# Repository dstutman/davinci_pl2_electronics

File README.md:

# Payload 2 for the DaVinci cubesat

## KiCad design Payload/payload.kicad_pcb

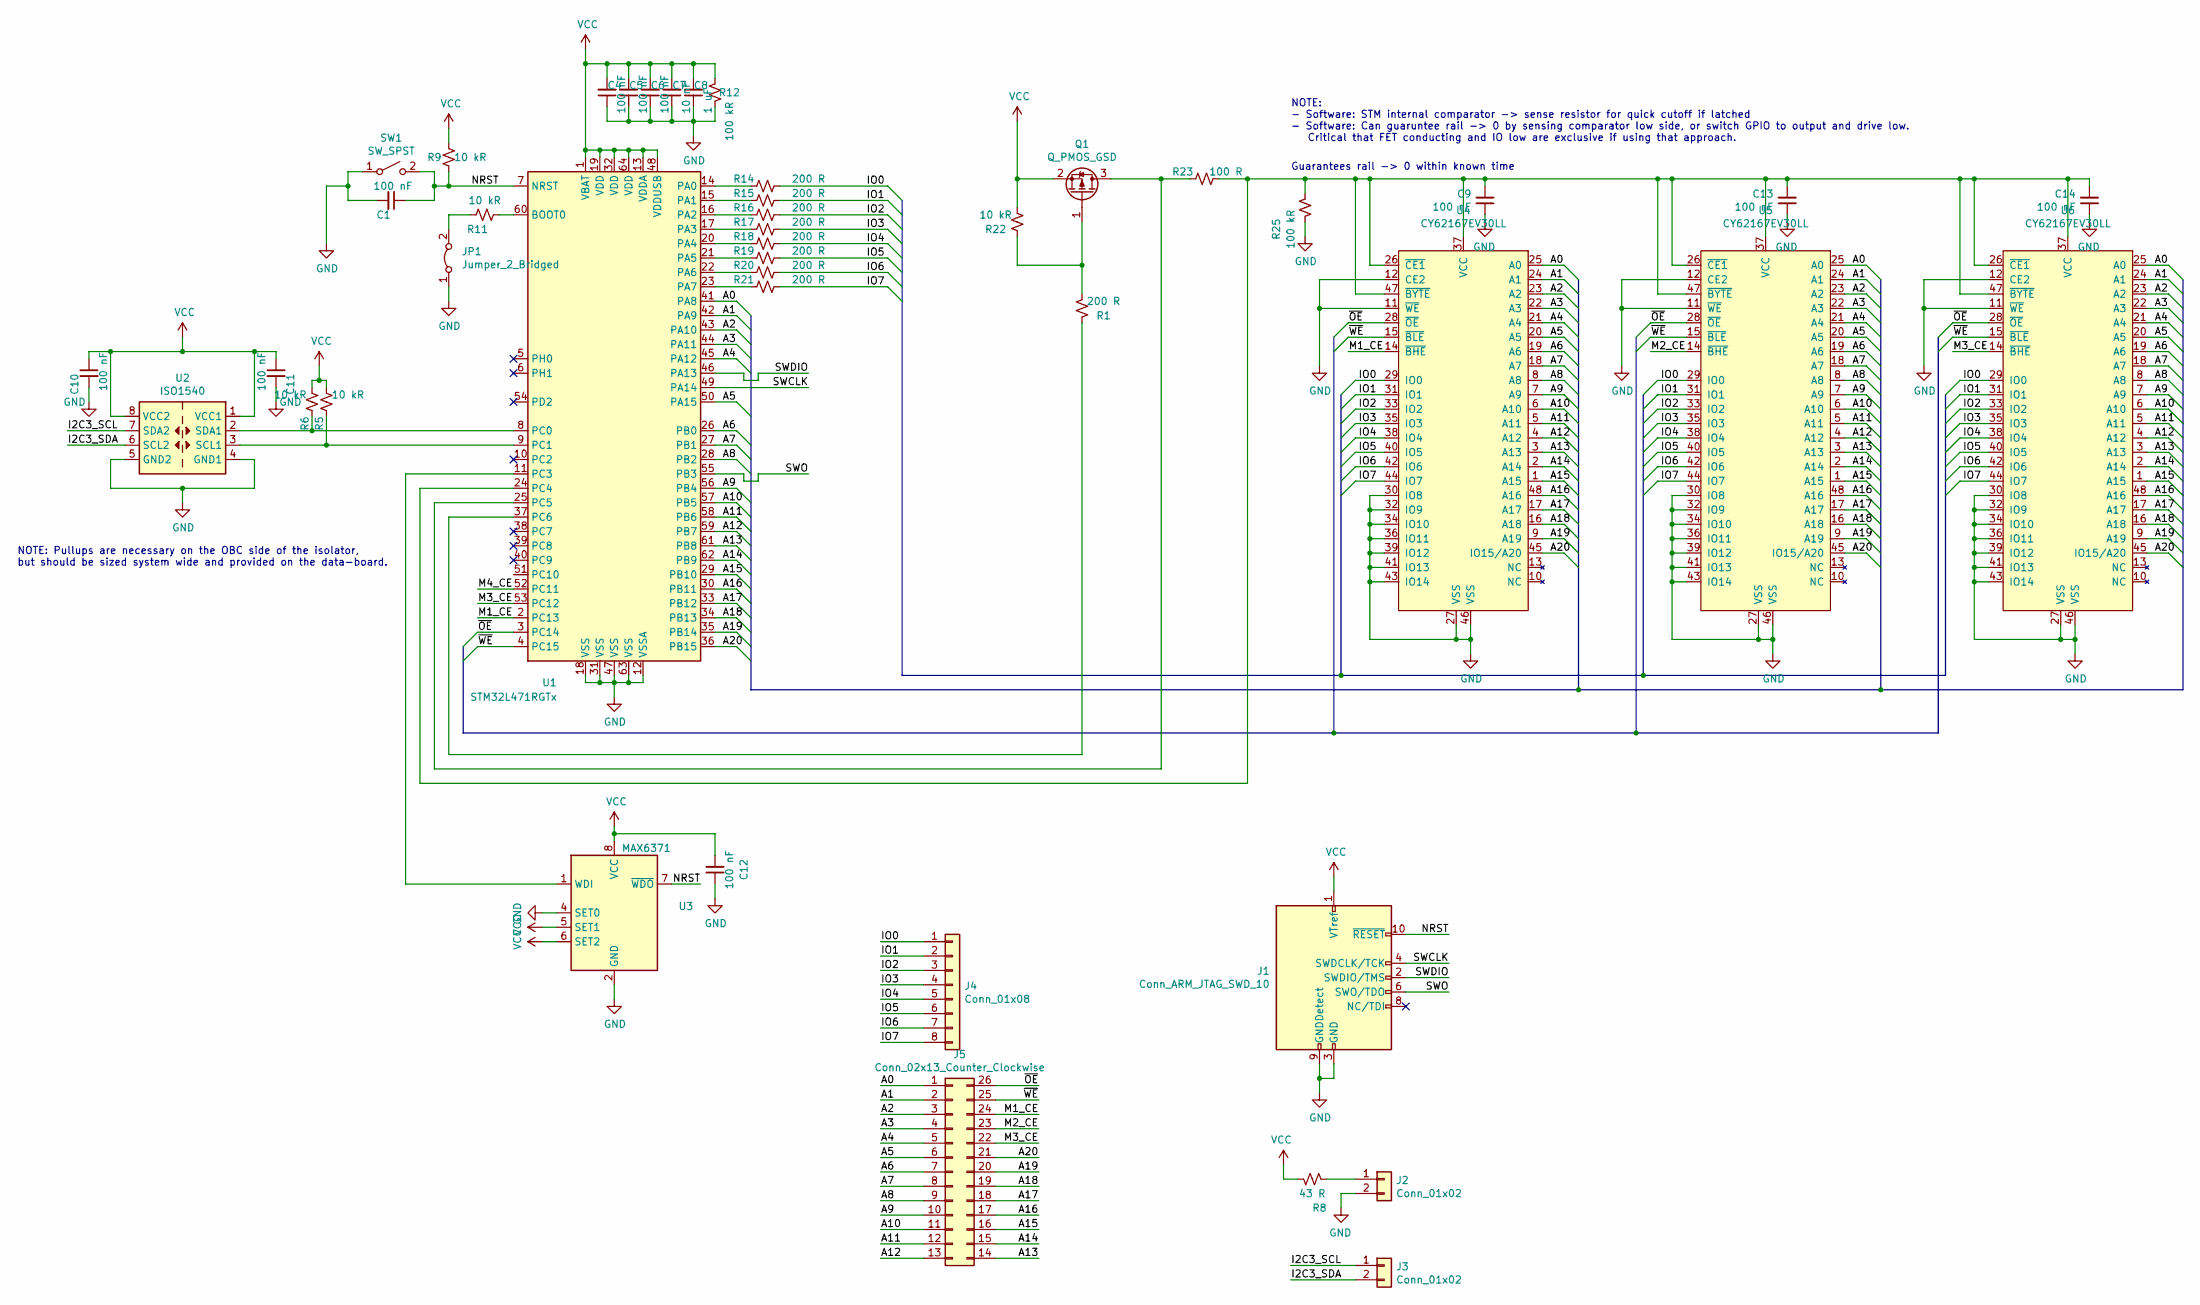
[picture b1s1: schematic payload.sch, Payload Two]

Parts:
C1, C4, C5, C6, C9, C10, C11, C12, C13, C14: 100 nF; C_0603_1608Metric
C7: 10 nF; C_0603_1608Metric
C8: 1 uF; C_0603_1608Metric
J1: Conn_ARM_JTAG_SWD_10; PinHeader_2x05_P1.27mm_Vertical
J2, J3: Conn_01x02; SolderWire-0.25sqmm_1x02_P4.5mm_D0.65mm_OD2mm
J4: Conn_01x08; PinHeader_1x08_P1.27mm_Vertical
J5: Conn_02x13_Counter_Clockwise; PinHeader_2x13_P1.27mm_Vertical
JP1: Jumper_2_Bridged; SolderJumper-2_P1.3mm_Bridged2Bar_RoundedPad1.0x1.5mm
Q1: Q_PMOS_GSD; SOT-23
R1, R14, R15, R16, R17, R18, R19, R20, R21: 200 R; R_0603_1608Metric
R5, R6, R9, R11, R22: 10 kR; R_0603_1608Metric
R8: 43 R; R_0603_1608Metric
R12, R25: 100 kR; R_0603_1608Metric
R23: 100 R; R_0603_1608Metric
SW1: SW_SPST; SW_SPST_PTS810
U1: STM32L471RGTx; LQFP-64_10x10mm_P0.5mm
U2: ISO1540; SOIC-8_3.9x4.9mm_P1.27mm
U3: MAX6371; SOT-23-8
U4, U5, U6: CY62167EV30LL; TSOP-I-48_18.4x12mm_P0.5mm

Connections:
/A0: J5.1, U1.41 (PA8), U4.25 (A0), U5.25 (A0), U6.25 (A0)
/A1: J5.2, U1.42 (PA9), U4.24 (A1), U5.24 (A1), U6.24 (A1)
/A2: J5.3, U1.43 (PA10), U4.23 (A2), U5.23 (A2), U6.23 (A2)
/A3: J5.4, U1.44 (PA11), U4.22 (A3), U5.22 (A3), U6.22 (A3)
/A4: J5.5, U1.45 (PA12), U4.21 (A4), U5.21 (A4), U6.21 (A4)
/A5: J5.6, U1.50 (PA15), U4.20 (A5), U5.20 (A5), U6.20 (A5)
/A6: J5.7, U1.26 (PB0), U4.19 (A6), U5.19 (A6), U6.19 (A6)
/A7: J5.8, U1.27 (PB1), U4.18 (A7), U5.18 (A7), U6.18 (A7)
/A8: J5.9, U1.28 (PB2), U4.8 (A8), U5.8 (A8), U6.8 (A8)
/A9: J5.10, U1.56 (PB4), U4.7 (A9), U5.7 (A9), U6.7 (A9)
/A10: J5.11, U1.57 (PB5), U4.6 (A10), U5.6 (A10), U6.6 (A10)
/A11: J5.12, U1.58 (PB6), U4.5 (A11), U5.5 (A11), U6.5 (A11)
/A12: J5.13, U1.59 (PB7), U4.4 (A12), U5.4 (A12), U6.4 (A12)
/A13: J5.14, U1.61 (PB8), U4.3 (A13), U5.3 (A13), U6.3 (A13)
/A14: J5.15, U1.62 (PB9), U4.2 (A14), U5.2 (A14), U6.2 (A14)
/A15: J5.16, U1.29 (PB10), U4.1 (A15), U5.1 (A15), U6.1 (A15)
/A16: J5.17, U1.30 (PB11), U4.48 (A16), U5.48 (A16), U6.48 (A16)
/A17: J5.18, U1.33 (PB12), U4.17 (A17), U5.17 (A17), U6.17 (A17)
/A18: J5.19, U1.34 (PB13), U4.16 (A18), U5.16 (A18), U6.16 (A18)
/A19: J5.20, U1.35 (PB14), U4.9 (A19), U5.9 (A19), U6.9 (A19)
/A20: J5.21, U1.36 (PB15), U4.45 (IO15/A20), U5.45 (IO15/A20), U6.45 (IO15/A20)
/I2C3_SCL: J3.1, U2.7 (SDA2)
/I2C3_SDA: J3.2, U2.6 (SCL2)
/IO0: J4.1, R14.1, U4.29 (IO0), U5.29 (IO0), U6.29 (IO0)
/IO1: J4.2, R15.1, U4.31 (IO1), U5.31 (IO1), U6.31 (IO1)
/IO2: J4.3, R16.1, U4.33 (IO2), U5.33 (IO2), U6.33 (IO2)
/IO3: J4.4, R17.1, U4.35 (IO3), U5.35 (IO3), U6.35 (IO3)
/IO4: J4.5, R18.1, U4.38 (IO4), U5.38 (IO4), U6.38 (IO4)
/IO5: J4.6, R19.1, U4.40 (IO5), U5.40 (IO5), U6.40 (IO5)
/IO6: J4.7, R20.1, U4.42 (IO6), U5.42 (IO6), U6.42 (IO6)
/IO7: J4.8, R21.1, U4.44 (IO7), U5.44 (IO7), U6.44 (IO7)
/M1_CE: J5.24, U1.2 (PC13), U4.14 (~BHE)
/M2_CE: J5.23, U5.14 (~BHE)
/M3_CE: J5.22, U1.53 (PC12), U6.14 (~BHE)
/M4_CE: U1.52 (PC11)
/NRST: C1.1, J1.10 (~RESET~), R9.2, SW1.2 (B), U1.7 (NRST), U3.7 (~WDO)
/SWCLK: J1.4 (SWDCLK/TCK), U1.49 (PA14)
/SWDIO: J1.2 (SWDIO/TMS), U1.46 (PA13)
/SWO: J1.6 (SWO/TDO), U1.55 (PB3)
/~OE: J5.26, U1.3 (PC14), U4.28 (~OE), U5.28 (~OE), U6.28 (~OE)
/~WE: J5.25, U1.4 (PC15), U4.15 (~BLE), U5.15 (~BLE), U6.15 (~BLE)
GND: C1.2, C4.1, C5.1, C6.1, C7.1, C8.1, C9.1, C10.2, C11.2, C12.1, C13.1, C14.1, J1.3 (GND), J1.5 (GND), J1.9 (GNDDetect), J2.2, JP1.1 (A), R12.2, R25.2, SW1.1 (A), U1.12 (VSSA), U1.18 (VSS), U1.31 (VSS), U1.47 (VSS), U1.63 (VSS), U2.4 (GND1), U2.5 (GND2), U3.2 (GND), U3.4 (SET0), U4.11 (~WE), U4.12 (CE2), U4.27 (VSS), U4.30 (IO8), U4.32 (IO9), U4.34 (IO10), U4.36 (IO11), U4.39 (IO12), U4.41 (IO13), U4.43 (IO14), U4.46 (VSS), U5.11 (~WE), U5.12 (CE2), U5.27 (VSS), U5.30 (IO8), U5.32 (IO9), U5.34 (IO10), U5.36 (IO11), U5.39 (IO12), U5.41 (IO13), U5.43 (IO14), U5.46 (VSS), U6.11 (~WE), U6.12 (CE2), U6.27 (VSS), U6.30 (IO8), U6.32 (IO9), U6.34 (IO10), U6.36 (IO11), U6.39 (IO12), U6.41 (IO13), U6.43 (IO14), U6.46 (VSS)
unnamed: C9.2, C13.2, C14.2, R23.2, R25.1, U1.24 (PC4), U4.26 (~CE1), U4.37 (VCC), U4.47 (~BYTE), U5.26 (~CE1), U5.37 (VCC), U5.47 (~BYTE), U6.26 (~CE1), U6.37 (VCC), U6.47 (~BYTE)
unnamed: J2.1, R8.2
unnamed: JP1.2 (B), R11.1
unnamed: Q1.1 (G), R1.2, R22.1
unnamed: Q1.3 (D), R23.1, U1.25 (PC5)
unnamed: R1.1, U1.37 (PC6)
unnamed: R5.2, U1.9 (PC1), U2.3 (SCL1)
unnamed: R6.2, U1.8 (PC0), U2.2 (SDA1)
unnamed: R11.2, U1.60 (BOOT0)
unnamed: R14.2, U1.14 (PA0)
unnamed: R15.2, U1.15 (PA1)
unnamed: R16.2, U1.16 (PA2)
unnamed: R17.2, U1.17 (PA3)
unnamed: R18.2, U1.20 (PA4)
unnamed: R19.2, U1.21 (PA5)
unnamed: R20.2, U1.22 (PA6)
unnamed: R21.2, U1.23 (PA7)
unnamed: U1.11 (PC3), U3.1 (WDI)
VCC: C4.2, C5.2, C6.2, C7.2, C8.2, C10.1, C11.1, C12.2, J1.1 (VTref), Q1.2 (S), R5.1, R6.1, R8.1, R9.1, R12.1, R22.2, U1.1 (VBAT), U1.13 (VDDA), U1.19 (VDD), U1.32 (VDD), U1.48 (VDDUSB), U1.64 (VDD), U2.1 (VCC1), U2.8 (VCC2), U3.5 (SET1), U3.6 (SET2), U3.8 (VCC)

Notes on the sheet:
NOTE: - Software: STM internal comparator -> sense resistor for quick cutoff if latched - Software: Can guaruntee rail -> 0 by sensing comparator low side, or switch GPIO to output and drive low. Critical that FET conducting and IO low are exclusive if using that approach.
Guarantees rail -> 0 within known time
NOTE: Pullups are necessary on the OBC side of the isolator, but should be sized system wide and provided on the data-board.

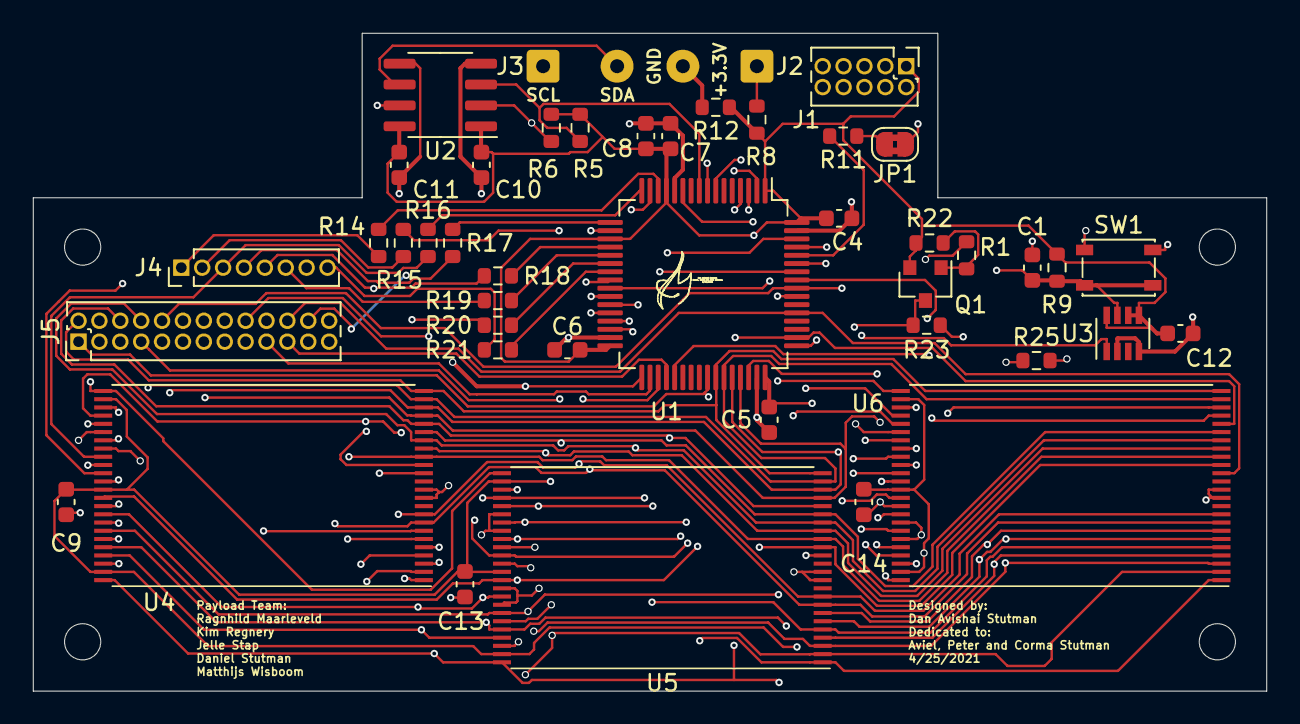
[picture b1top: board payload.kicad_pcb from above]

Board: 4 copper layers, 75.0 x 40.0 mm, 44 parts (0 on the bottom side), 60 nets.

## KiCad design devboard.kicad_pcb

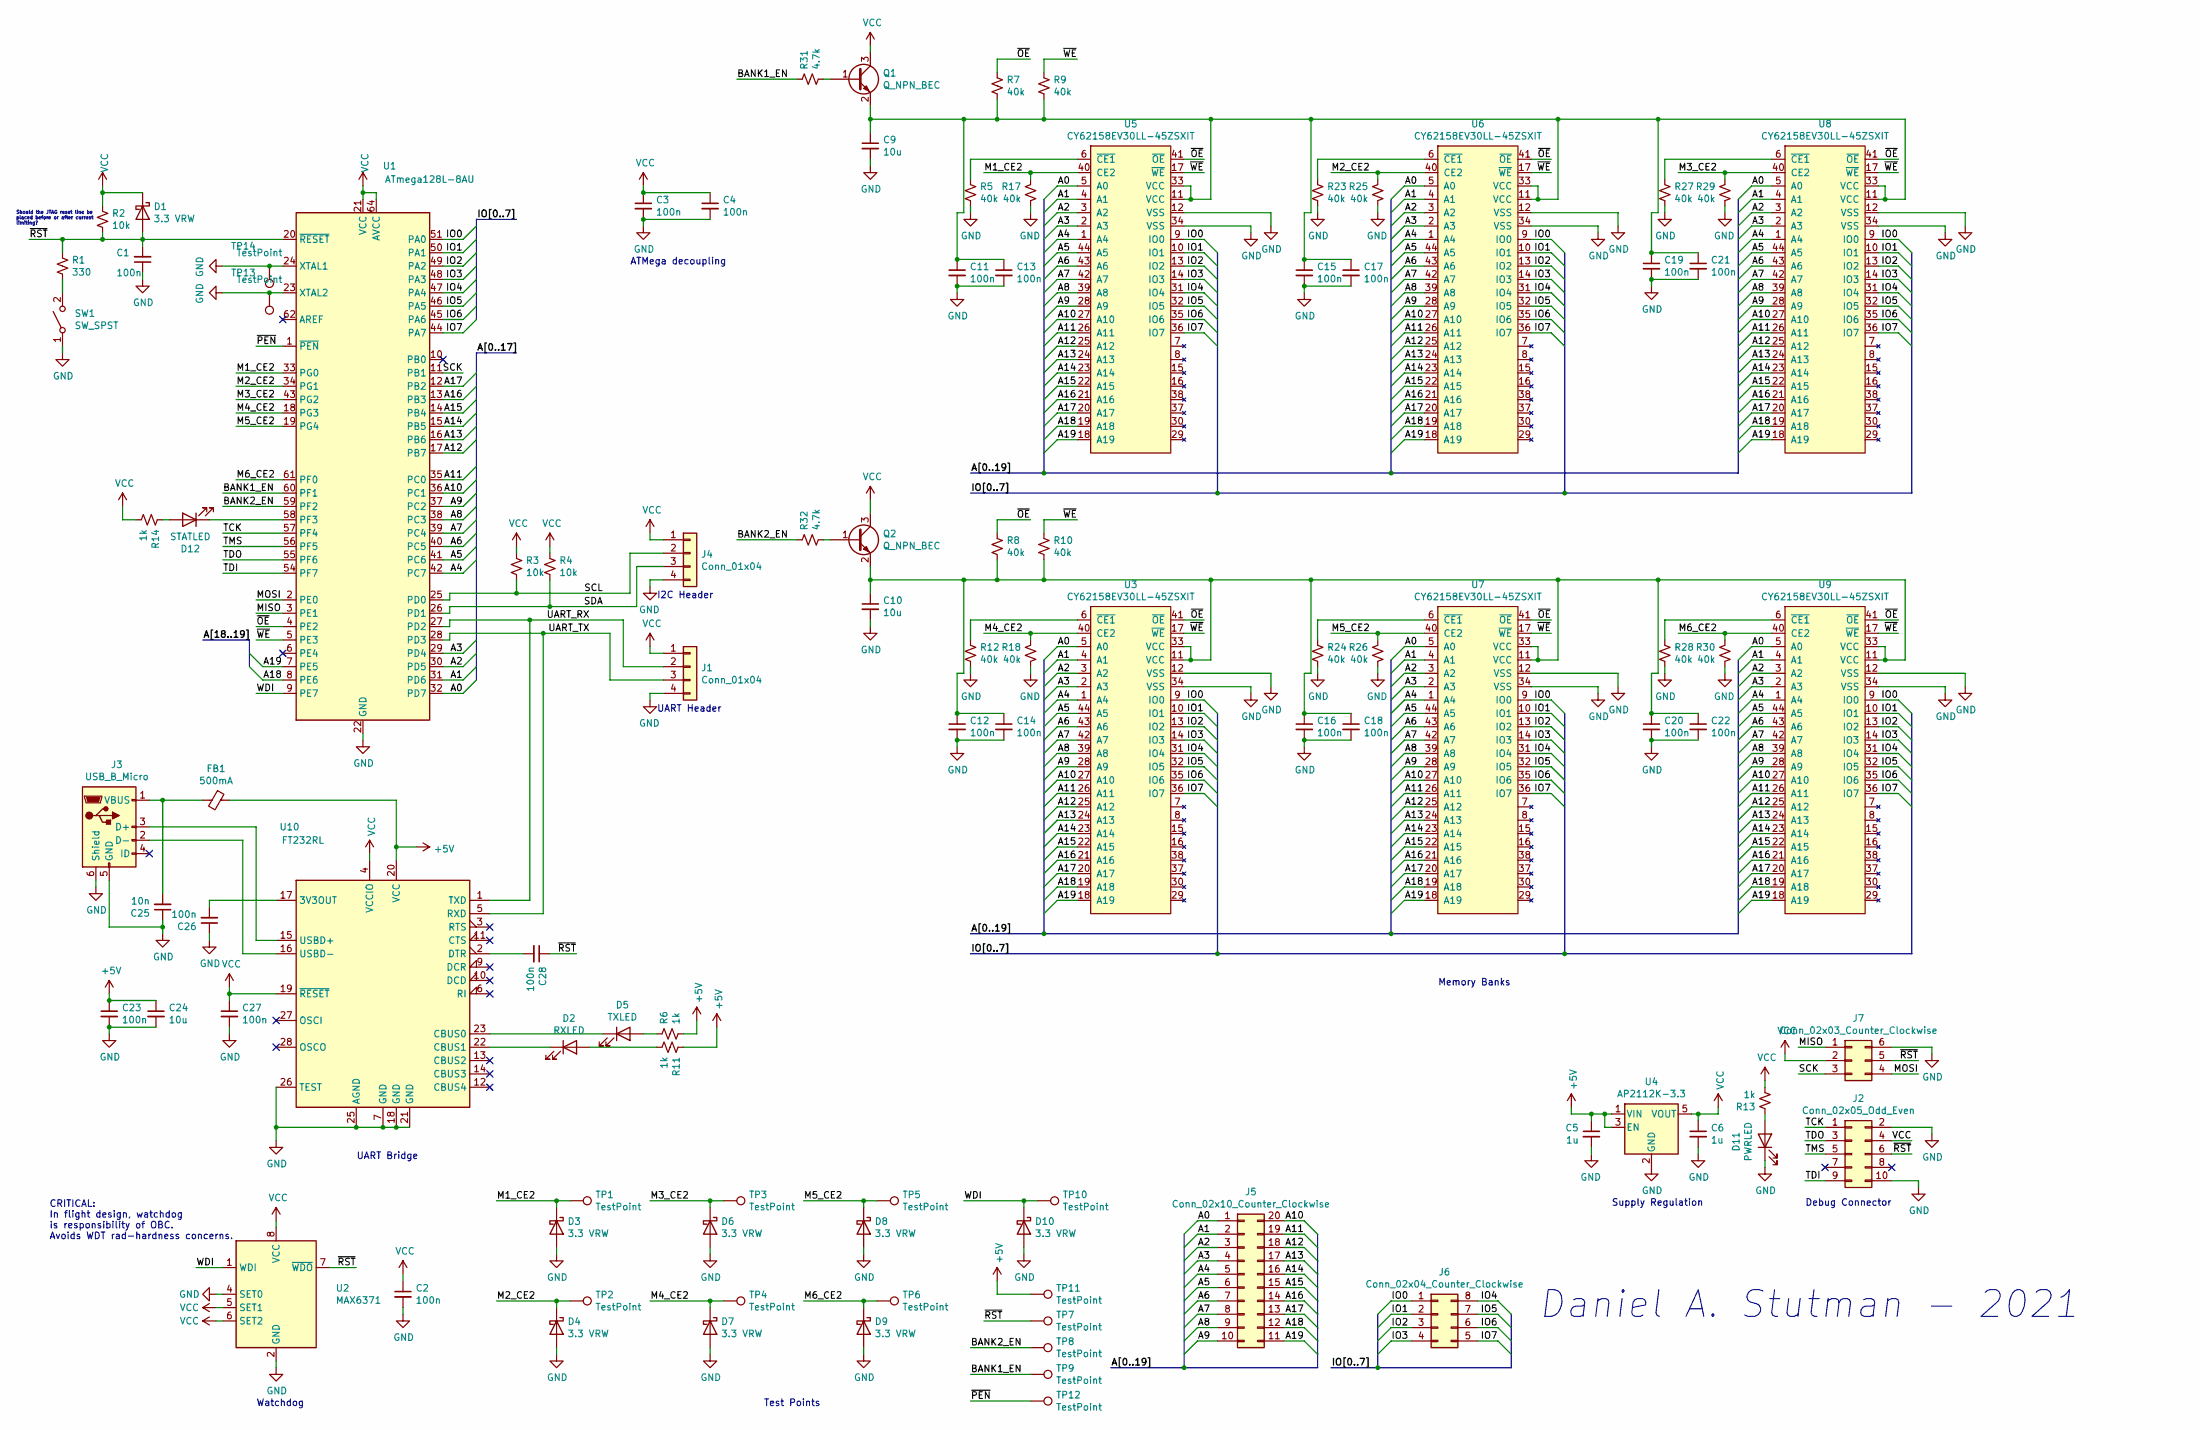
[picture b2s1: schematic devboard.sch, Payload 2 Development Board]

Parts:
C1, C2, C3, C4, C11, C12, C13, C14, C15, C16, C17, C18, C19, C20, C21, C22, C23, C26, C27, C28: 100n; C_0603_1608Metric_Pad1.08x0.95mm_HandSolder
C5, C6: 1u; C_0603_1608Metric_Pad1.08x0.95mm_HandSolder
C9, C10, C24: 10u; C_0603_1608Metric_Pad1.08x0.95mm_HandSolder
C25: 10n; C_0603_1608Metric_Pad1.08x0.95mm_HandSolder
D1, D3, D4, D6, D7, D8, D9, D10: 3.3 VRW; D_SOD-923
D2: RXLED; LED_0603_1608Metric_Castellated
D5: TXLED; LED_0603_1608Metric_Castellated
D11: PWRLED; LED_0603_1608Metric_Castellated
D12: STATLED; LED_0603_1608Metric_Castellated
FB1: 500mA; L_0603_1608Metric_Pad1.05x0.95mm_HandSolder
J1, J4: Conn_01x04; PinHeader_1x04_P2.54mm_Vertical
J2: Conn_02x05_Odd_Even; PinHeader_2x05_P1.27mm_Vertical
J3: USB_B_Micro; USB_Micro-B_Wuerth_629105150521
J5: Conn_02x10_Counter_Clockwise; PinHeader_2x10_P2.54mm_Vertical
J6: Conn_02x04_Counter_Clockwise; PinHeader_2x04_P2.54mm_Vertical
J7: Conn_02x03_Counter_Clockwise; PinHeader_2x03_P1.27mm_Vertical
Q1, Q2: Q_NPN_BEC; SOT-23
R1: 330; R_0603_1608Metric_Pad0.98x0.95mm_HandSolder
R2, R3, R4: 10k; R_0603_1608Metric_Pad0.98x0.95mm_HandSolder
R5, R7, R8, R9, R10, R12, R17, R18, R23, R24, R25, R26, R27, R28, R29, R30: 40k; R_0603_1608Metric_Pad0.98x0.95mm_HandSolder
R6, R11, R13, R14: 1k; R_0603_1608Metric_Pad0.98x0.95mm_HandSolder
R31, R32: 4.7k; R_0603_1608Metric_Pad0.98x0.95mm_HandSolder
SW1: SW_SPST; SW_SPST_PTS810
TP1, TP2, TP3, TP4, TP5, TP6, TP7, TP8, TP9, TP10, TP11, TP12: TestPoint; PinHeader_1x01_P2.54mm_Vertical
TP13, TP14: TestPoint; TestPoint_Bridge_Pitch2.54mm_Drill0.7mm
U1: ATmega128L-8AU; TQFP-64_14x14mm_P0.8mm
U2: MAX6371; SOT-23-8
U3, U5, U6, U7, U8, U9: CY62158EV30LL-45ZSXIT; TSOP-II-44_10.16x18.41mm_P0.8mm
U4: AP2112K-3.3; SOT-23-5
U10: FT232RL; SSOP-28_5.3x10.2mm_P0.65mm

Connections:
+5V: C5.1, C23.1, C24.1, FB1.1, R6.2, R11.1, TP11.1, U4.1 (VIN), U4.3 (EN), U10.20 (VCC)
/A0: J5.1, U1.32 (PD7), U3.5 (A0), U5.5 (A0), U6.5 (A0), U7.5 (A0), U8.5 (A0), U9.5 (A0)
/A1: J5.2, U1.31 (PD6), U3.4 (A1), U5.4 (A1), U6.4 (A1), U7.4 (A1), U8.4 (A1), U9.4 (A1)
/A2: J5.3, U1.30 (PD5), U3.3 (A2), U5.3 (A2), U6.3 (A2), U7.3 (A2), U8.3 (A2), U9.3 (A2)
/A3: J5.4, U1.29 (PD4), U3.2 (A3), U5.2 (A3), U6.2 (A3), U7.2 (A3), U8.2 (A3), U9.2 (A3)
/A4: J5.5, U1.42 (PC7), U3.1 (A4), U5.1 (A4), U6.1 (A4), U7.1 (A4), U8.1 (A4), U9.1 (A4)
/A5: J5.6, U1.41 (PC6), U3.44 (A5), U5.44 (A5), U6.44 (A5), U7.44 (A5), U8.44 (A5), U9.44 (A5)
/A6: J5.7, U1.40 (PC5), U3.43 (A6), U5.43 (A6), U6.43 (A6), U7.43 (A6), U8.43 (A6), U9.43 (A6)
/A7: J5.8, U1.39 (PC4), U3.42 (A7), U5.42 (A7), U6.42 (A7), U7.42 (A7), U8.42 (A7), U9.42 (A7)
/A8: J5.9, U1.38 (PC3), U3.39 (A8), U5.39 (A8), U6.39 (A8), U7.39 (A8), U8.39 (A8), U9.39 (A8)
/A9: J5.10, U1.37 (PC2), U3.28 (A9), U5.28 (A9), U6.28 (A9), U7.28 (A9), U8.28 (A9), U9.28 (A9)
/A10: J5.20, U1.36 (PC1), U3.27 (A10), U5.27 (A10), U6.27 (A10), U7.27 (A10), U8.27 (A10), U9.27 (A10)
/A11: J5.19, U1.35 (PC0), U3.26 (A11), U5.26 (A11), U6.26 (A11), U7.26 (A11), U8.26 (A11), U9.26 (A11)
/A12: J5.18, U1.17 (PB7), U3.25 (A12), U5.25 (A12), U6.25 (A12), U7.25 (A12), U8.25 (A12), U9.25 (A12)
/A13: J5.17, U1.16 (PB6), U3.24 (A13), U5.24 (A13), U6.24 (A13), U7.24 (A13), U8.24 (A13), U9.24 (A13)
/A14: J5.16, U1.15 (PB5), U3.23 (A14), U5.23 (A14), U6.23 (A14), U7.23 (A14), U8.23 (A14), U9.23 (A14)
/A15: J5.15, U1.14 (PB4), U3.22 (A15), U5.22 (A15), U6.22 (A15), U7.22 (A15), U8.22 (A15), U9.22 (A15)
/A16: J5.14, U1.13 (PB3), U3.21 (A16), U5.21 (A16), U6.21 (A16), U7.21 (A16), U8.21 (A16), U9.21 (A16)
/A17: J5.13, U1.12 (PB2), U3.20 (A17), U5.20 (A17), U6.20 (A17), U7.20 (A17), U8.20 (A17), U9.20 (A17)
/A18: J5.12, U1.8 (PE6), U3.19 (A18), U5.19 (A18), U6.19 (A18), U7.19 (A18), U8.19 (A18), U9.19 (A18)
/A19: J5.11, U1.7 (PE5), U3.18 (A19), U5.18 (A19), U6.18 (A19), U7.18 (A19), U8.18 (A19), U9.18 (A19)
/BANK1_EN: R31.1, TP9.1, U1.60 (PF1)
/BANK2_EN: R32.1, TP8.1, U1.59 (PF2)
/IO0: J6.1, U1.51 (PA0), U3.9 (IO0), U5.9 (IO0), U6.9 (IO0), U7.9 (IO0), U8.9 (IO0), U9.9 (IO0)
/IO1: J6.2, U1.50 (PA1), U3.10 (IO1), U5.10 (IO1), U6.10 (IO1), U7.10 (IO1), U8.10 (IO1), U9.10 (IO1)
/IO2: J6.3, U1.49 (PA2), U3.13 (IO2), U5.13 (IO2), U6.13 (IO2), U7.13 (IO2), U8.13 (IO2), U9.13 (IO2)
/IO3: J6.4, U1.48 (PA3), U3.14 (IO3), U5.14 (IO3), U6.14 (IO3), U7.14 (IO3), U8.14 (IO3), U9.14 (IO3)
/IO4: J6.8, U1.47 (PA4), U3.31 (IO4), U5.31 (IO4), U6.31 (IO4), U7.31 (IO4), U8.31 (IO4), U9.31 (IO4)
/IO5: J6.7, U1.46 (PA5), U3.32 (IO5), U5.32 (IO5), U6.32 (IO5), U7.32 (IO5), U8.32 (IO5), U9.32 (IO5)
/IO6: J6.6, U1.45 (PA6), U3.35 (IO6), U5.35 (IO6), U6.35 (IO6), U7.35 (IO6), U8.35 (IO6), U9.35 (IO6)
/IO7: J6.5, U1.44 (PA7), U3.36 (IO7), U5.36 (IO7), U6.36 (IO7), U7.36 (IO7), U8.36 (IO7), U9.36 (IO7)
/M1_CE2: D3.1 (K), R17.2, TP1.1, U1.33 (PG0), U5.40 (CE2)
/M2_CE2: D4.1 (K), R25.2, TP2.1, U1.34 (PG1), U6.40 (CE2)
/M3_CE2: D6.1 (K), R29.2, TP3.1, U1.43 (PG2), U8.40 (CE2)
/M4_CE2: D7.1 (K), R18.2, TP4.1, U1.18 (PG3), U3.40 (CE2)
/M5_CE2: D8.1 (K), R26.2, TP5.1, U1.19 (PG4), U7.40 (CE2)
/M6_CE2: D9.1 (K), R30.2, TP6.1, U1.61 (PF0), U9.40 (CE2)
/MISO: J7.1, U1.3 (PE1)
/MOSI: J7.4, U1.2 (PE0)
/SCK: J7.3, U1.11 (PB1)
/SCL: J4.2, R3.2, U1.25 (PD0)
/SDA: J4.3, R4.2, U1.26 (PD1)
/TCK: J2.1, U1.57 (PF4)
/TDI: J2.9, U1.54 (PF7)
/TDO: J2.3, U1.55 (PF6)
/TMS: J2.5, U1.56 (PF5)
/UART_RX: J1.2, U1.27 (PD2), U10.1 (TXD)
/UART_TX: J1.3, U1.28 (PD3), U10.5 (RXD)
/WDI: D10.1 (K), TP10.1, U1.9 (PE7), U2.1 (WDI)
/~OE: R7.2, R8.2, U1.4 (PE2), U3.41 (~OE), U5.41 (~OE), U6.41 (~OE), U7.41 (~OE), U8.41 (~OE), U9.41 (~OE); also elsewhere on the board
/~PEN: TP12.1, U1.1 (~PEN)
/~RST: C1.2, C28.1, D1.2 (A), J2.6, J7.5, R1.1, R2.2, TP7.1, U1.20 (~RESET), U2.7 (~WDO)
/~WE: R9.2, R10.2, U1.5 (PE3), U3.17 (~WE), U5.17 (~WE), U6.17 (~WE), U7.17 (~WE), U8.17 (~WE), U9.17 (~WE); also elsewhere on the board
GND: C1.1, C2.2, C3.2, C4.2, C5.2, C6.2, C9.2, C10.2, C11.2, C12.2, C13.2, C14.2, C15.2, C16.2, C17.2, C18.2, C19.2, C20.2, C21.2, C22.2, C23.2, C24.2, C25.1, C26.1, C27.2, D3.2 (A), D4.2 (A), D6.2 (A), D7.2 (A), D8.2 (A), D9.2 (A), D10.2 (A), D11.1 (K), J1.4, J2.2, J2.10, J3.5 (GND), J3.6 (Shield), J4.4, J7.6, R5.1, R12.1, R17.1, R18.1, R23.1, R24.1, R25.1, R26.1, R27.1, R28.1, R29.1, R30.1, SW1.1 (A), TP13.1, TP14.1, U1.22 (GND), U1.23 (XTAL2), U1.24 (XTAL1), U1.53 (GND), U1.63 (GND), U2.2 (GND), U2.4 (SET0), U3.12 (VSS), U3.34 (VSS), U4.2 (GND), U5.12 (VSS), U5.34 (VSS), U6.12 (VSS), U6.34 (VSS), U7.12 (VSS), U7.34 (VSS), U8.12 (VSS), U8.34 (VSS), U9.12 (VSS), U9.34 (VSS), U10.7 (GND), U10.18 (GND), U10.21 (GND), U10.25 (AGND), U10.26 (TEST)
unnamed: C10.1, C12.1, C14.1, C16.1, C18.1, C20.1, C22.1, Q2.2 (E), R8.1, R10.1, U3.11 (VCC), U3.33 (VCC), U7.11 (VCC), U7.33 (VCC), U9.11 (VCC), U9.33 (VCC)
unnamed: C9.1, C11.1, C13.1, C15.1, C17.1, C19.1, C21.1, Q1.2 (E), R7.1, R9.1, U5.11 (VCC), U5.33 (VCC), U6.11 (VCC), U6.33 (VCC), U8.11 (VCC), U8.33 (VCC)
unnamed: C25.2, FB1.2, J3.1 (VBUS)
unnamed: C26.2, U10.17 (3V3OUT)
unnamed: C28.2, U10.2 (DTR)
unnamed: D2.1 (K), U10.22 (CBUS1)
unnamed: D2.2 (A), R11.2
unnamed: D5.1 (K), U10.23 (CBUS0)
unnamed: D5.2 (A), R6.1
unnamed: D11.2 (A), R13.1
unnamed: D12.1 (K), U1.58 (PF3)
unnamed: D12.2 (A), R14.1
unnamed: J3.2 (D-), U10.16 (USBD-)
unnamed: J3.3 (D+), U10.15 (USBD+)
unnamed: Q1.1 (B), R31.2
unnamed: Q2.1 (B), R32.2
unnamed: R1.2, SW1.2 (B)
unnamed 74: R5.2, U5.6 (~CE1); also elsewhere on the board
unnamed 75: R12.2, U3.6 (~CE1); also elsewhere on the board
unnamed 76: R23.2, U6.6 (~CE1); also elsewhere on the board
unnamed 77: R24.2, U7.6 (~CE1); also elsewhere on the board
unnamed 78: R27.2, U8.6 (~CE1); also elsewhere on the board
unnamed 79: R28.2, U9.6 (~CE1); also elsewhere on the board
VCC: C2.1, C3.1, C4.1, C6.1, C27.1, D1.1 (K), J1.1, J2.4, J4.1, J7.2, Q1.3 (C), Q2.3 (C), R2.1, R3.1, R4.1, R13.2, R14.2, U1.21 (VCC), U1.52 (VCC), U1.64 (AVCC), U2.5 (SET1), U2.6 (SET2), U2.8 (VCC), U4.5 (VOUT), U10.4 (VCCIO), U10.19 (~RESET~)

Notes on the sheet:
ATMega decoupling
Should the JTAG reset line be placed before or after current limiting?
Watchdog
CRITICAL: In flight design, watchdog is responsibility of OBC. Avoids WDT rad-hardness concerns.
UART Header
I2C Header
Supply Regulation
Debug Connector
Test Points
UART Bridge
Daniel A. Stutman - 2021
Memory Banks

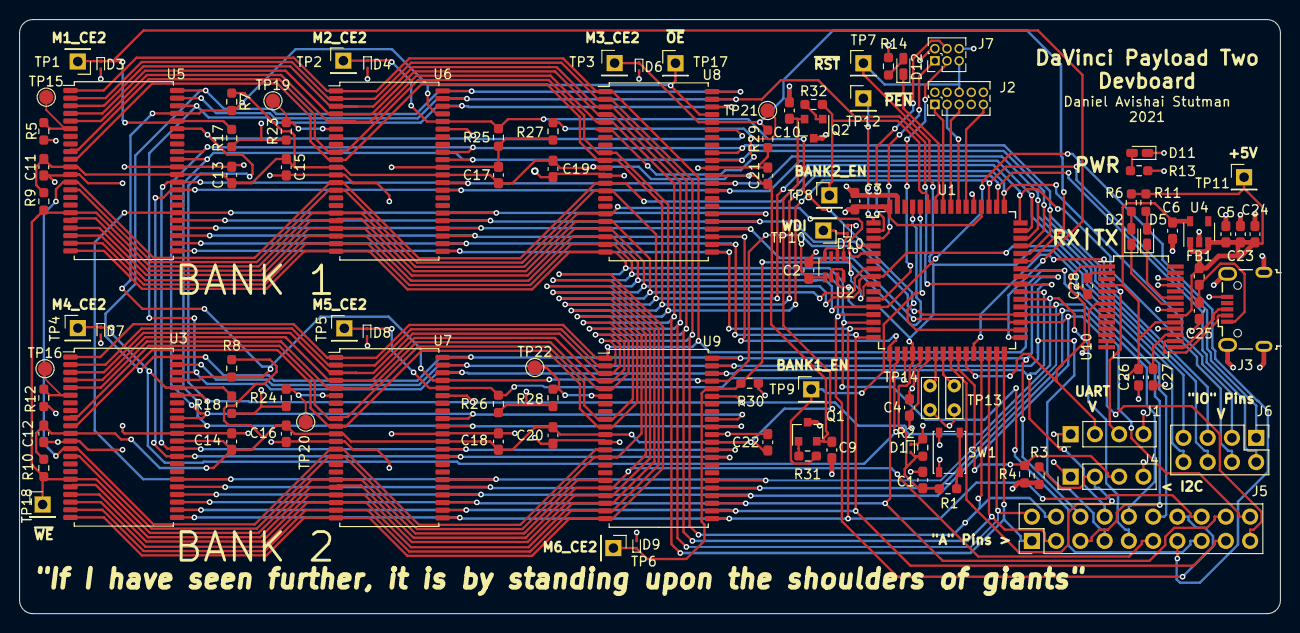
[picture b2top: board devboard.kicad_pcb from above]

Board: 4 copper layers, 132.1 x 62.2 mm, 107 parts (0 on the bottom side), 78 nets.

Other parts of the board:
TP15, TP16, TP19, TP20, TP21, TP22: TestPoint; TestPoint_Pad_D1.5mm
TP17, TP18: TestPoint; PinHeader_1x01_P2.54mm_Vertical

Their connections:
/~OE: TP17.1; also elsewhere on the board
/~WE: TP18.1; also elsewhere on the board
unnamed 74: TP15.1; also elsewhere on the board
unnamed 75: TP16.1; also elsewhere on the board
unnamed 76: TP19.1; also elsewhere on the board
unnamed 77: TP20.1; also elsewhere on the board
unnamed 78: TP21.1; also elsewhere on the board
unnamed 79: TP22.1; also elsewhere on the board

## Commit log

2020-12-19 Add hardware projects
2020-12-19 Add documentation and initial work on devboard
2020-12-19 Tie xtal pins to ground for now
2020-12-19 Add memory banks
2020-12-20 Add more memory, watchdog, buffers, test points
2020-12-20 Add LDO for 5V supply
2020-12-20 Add breakout header
2020-12-20 Complete draft schematic
2020-12-21 Fix critical error
2020-12-29 Work on SRAMBB prototype
2021-01-03 Improved supercap circuit
2021-01-08 Remove gitattributes
2021-01-08 Move to new project structure
2021-01-09 Rename documents folder
2021-01-10 Remove backup power section
2021-01-10 Add CY62158EV30 footprint
2021-01-10 Reorder pins on Cypress SRAM
2021-01-10 Complete SRAM schematic draft
2021-01-10 Correct errors and assign footprints
2021-01-10 Correct BJT base resistors values
2021-01-10 Change schematic title
2021-01-10 Add 5V testpoint
2021-01-10 Improve schematic labeling
2021-01-10 Remove bad old smudge filter note
2021-01-11 Fix attribution
2021-01-11 Fix UART lines
2021-01-11 Mark unconnected pins
2021-01-11 Improve .gitignore and change plot directory
2021-01-11 Schematic cohesion improvements
2021-01-14 Fix memory decoupling
2021-01-14 Exploration into bus layout
    This commit made to save progress before attempting new layout.
2021-01-14 Fix missing pin assignments and excessive pulls
2021-01-14 Successfully route memories
2021-01-14 Join memory busses
2021-01-15 Routing almost complete
2021-01-15 Autorouting pass
2021-01-15 Improve silk
2021-01-15 Slight via improvements
2021-01-15 Rounded borders
2021-01-15 Labeling correction
2021-01-16 Fix pullup connections and minor silk alterations
2021-01-16 Add power indicator and improve silk
2021-01-16 Net cleanup
    Ran the KiCAD net cleanup tool with all options enabled. This created
    a lot of commit noise, but none of this functionally changes the circit.
2021-01-16 Annotation update
2021-01-16 Remove extraneous wire
2021-01-16 SPI programming and silk improvements
2021-01-17 Add crystal pads, MCU LED, fix serial routing
2021-01-17 Add more testpoints
    Just in case the Cypress chip operates differently than advertised.
2021-01-17 Small fixes to clock pads
2021-02-07 Move devboard into new directory structure
2021-02-07 Initialize payload project
2021-02-08 Add symbols for HiRel memories
2021-02-08 Add initial notes
2021-03-01 Work on power control for memory module
    Forgot to commit so this is old, I believe this is what changed.
2021-03-03 Work on inter-board connectors
2021-03-10 Work on new single board design with commercial MCU.
2021-03-14 Work on bus and power
2021-03-14 Progress on bus
2021-03-16 Hook up chip controls and some power stuff
2021-03-22 Current limiting resistor and implementation notes
2021-03-22 Add additional TODO
2021-03-28 Testpoints, specific values, CE, series protection, crystal, headers.
2021-04-01 Connectors, notes, general cleanup
2021-04-02 Fix missing gate resistors
2021-04-18 Add I2C isolation
2021-04-20 Add watchdog and I2C isolator
2021-04-20 Replace old memory symbol
2021-04-22 Cosmetic changes
2021-04-22 Assign footprints
2021-04-22 Schematic fixes and routing
2021-04-25 Partial routing
2021-04-25 Reduced BOM to fit, routed
2021-04-25 Silk corrections and fix routes
2021-04-26 Correct silk violations
2021-04-30 Modify silk
2021-05-01 Update component values and isolator
2021-05-01 Tweak
